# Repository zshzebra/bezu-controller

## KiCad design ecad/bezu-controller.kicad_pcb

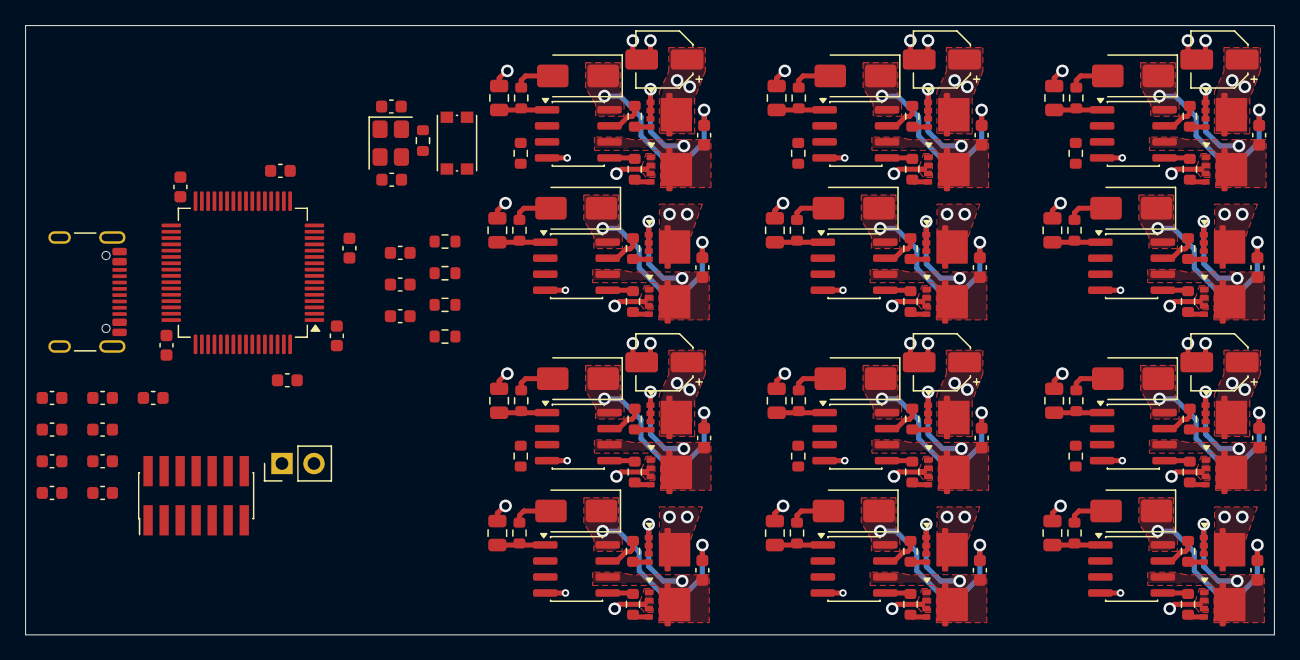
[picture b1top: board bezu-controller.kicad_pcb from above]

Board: 4 copper layers, 99.0 x 48.3 mm, 151 parts (0 on the bottom side), 109 nets.

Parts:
C1, C4, C7, C10, C13, C16, C19, C22, C25, C28, C31, C34: 470nF; C_0805_2012Metric
C2, C5, C8, C11, C14, C17, C20, C23, C26, C29, C32, C35: 47nF; C_0603_1608Metric
C6, C12, C18, C24, C30, C36: 4.7uF; CP_Elec_4x5.4
C37: 4.7uF; C_0603_1608Metric
C38, C39: 2.2uF; C_0603_1608Metric
C40, C41, C42, C43, C44, C45, C46, C47, C48, C49, C50, C51, C52, C53, C54: 100nF; C_0603_1608Metric
C55, C56: 16pF; C_0603_1608Metric
D1, D2, D3, D4, D5, D6, D7, D8, D9, D10, D11, D12: ES1D; D_SMA
J1: ST_STDC14; PinHeader_2x07_P1.27mm_Vertical_SMD
J2: GCT 4105; USB_C_Receptacle_GCT_USB4105-xx-A_16P_TopMnt_Horizontal
J3: Conn_01x02; PinHeader_1x02_P2.54mm_Vertical
Q1, Q2, Q3, Q4, Q5, Q6, Q7, Q8, Q9, Q10, Q11, Q12, Q13, Q14, Q15, Q16, Q17, Q18, Q19, Q20, Q21, Q22, Q23, Q24: 40N06D; PDFN3x3
R1, R8, R15, R22, R29, R36, R43, R47: 10K; R_0603_1608Metric
R2, R5, R9, R12, R16, R19, R23, R26, R30, R33, R37, R40: 2.2R; R_0603_1608Metric
R3, R4, R6, R7, R10, R11, R13, R14, R17, R18, R20, R21, R24, R25, R27, R28, R31, R32, R34, R35, R38, R39, R41, R42: 10R; R_0603_1608Metric
R44: 100R; R_0603_1608Metric
R45, R46: 5k1; R_0603_1608Metric
SW1: SW_Push; SW_Push_1P1T_NO_CK_KMR2
U1, U2, U3, U4, U5, U6, U7, U8, U9, U10, U11, U12: IR2104; SOIC-8_3.9x4.9mm_P1.27mm
U13: STM32F405RGTx; LQFP-64_10x10mm_P0.5mm
Y1: 12MHz; Crystal_SMD_3225-4Pin_3.2x2.5mm

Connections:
+3.3V: C37.1, C40.1, C41.1, C42.1, C43.1, C44.1, C45.1, C46.1, C47.1, C48.1, C49.1, C50.1, C51.1, C52.1, C53.1, C54.1, J1.3 (VCC), R43.1, R47.1, U13.1 (VBAT), U13.13 (VDDA), U13.19 (VDD), U13.32 (VDD), U13.48 (VDD), U13.64 (VDD)
+5V: J2.A4 (VBUS), J2.A9 (VBUS), J2.B4 (VBUS), J2.B9 (VBUS)
+12V: C1.1, C4.1, C7.1, C10.1, C13.1, C16.1, C19.1, C22.1, C25.1, C28.1, C31.1, C34.1, R2.1, R5.1, R9.1, R12.1, R16.1, R19.1, R23.1, R26.1, R30.1, R33.1, R37.1, R40.1, U1.1 (VCC), U2.1 (VCC), U3.1 (VCC), U4.1 (VCC), U5.1 (VCC), U6.1 (VCC), U7.1 (VCC), U8.1 (VCC), U9.1 (VCC), U10.1 (VCC), U11.1 (VCC), U12.1 (VCC)
/-PITCH H-Bridge/OUT1: C2.2, Q1.S, Q2.D, U1.6 (VS)
/-PITCH H-Bridge/OUT2: C5.2, Q3.S, Q4.D, U2.6 (VS)
/-PITCH H-Bridge/~SD: R1.1, U1.3 (~SD), U2.3 (~SD)
/-ROLL H-Bridge1/OUT1: C14.2, Q9.S, Q10.D, U5.6 (VS)
/-ROLL H-Bridge1/OUT2: C17.2, Q11.S, Q12.D, U6.6 (VS)
/-ROLL H-Bridge1/~SD: R15.1, U5.3 (~SD), U6.3 (~SD)
/-YAW H-Bridge2/OUT1: C26.2, Q17.S, Q18.D, U9.6 (VS)
/-YAW H-Bridge2/OUT2: C29.2, Q19.S, Q20.D, U10.6 (VS)
/-YAW H-Bridge2/~SD: R29.1, U9.3 (~SD), U10.3 (~SD)
/MCU/BOOT0: J3.1, R47.2, U13.60 (BOOT0)
/MCU/PH0: C56.1, U13.5 (PH0), Y1.3
/MCU/PH1: C55.1, U13.6 (PH1), Y1.1
/MCU/SWCLK: J1.6 (JCLK/SWCLK), U13.49 (PA14)
/MCU/SWDIO: J1.4 (JTMS/SWDIO), U13.46 (PA13)
/MCU/SWO: J1.8 (JTDO/SWO), U13.55 (PB3)
/MCU/USB_DM: J2.A7 (D-), J2.B7 (D-), U13.44 (PA11)
/MCU/USB_DP: J2.A6 (D+), J2.B6 (D+), U13.45 (PA12)
/PITCH H-Bridge1/OUT1: C8.2, Q5.S, Q6.D, U3.6 (VS)
/PITCH H-Bridge1/OUT2: C11.2, Q7.S, Q8.D, U4.6 (VS)
/PITCH H-Bridge1/~SD: R8.1, U3.3 (~SD), U4.3 (~SD)
/ROLL H-Bridge2/OUT1: C20.2, Q13.S, Q14.D, U7.6 (VS)
/ROLL H-Bridge2/OUT2: C23.2, Q15.S, Q16.D, U8.6 (VS)
/ROLL H-Bridge2/~SD: R22.1, U7.3 (~SD), U8.3 (~SD)
/YAW H-Bridge3/OUT1: C32.2, Q21.S, Q22.D, U11.6 (VS)
/YAW H-Bridge3/OUT2: C35.2, Q23.S, Q24.D, U12.6 (VS)
/YAW H-Bridge3/~SD: R36.1, U11.3 (~SD), U12.3 (~SD)
GND: C1.2, C4.2, C6.2, C7.2, C10.2, C12.2, C13.2, C16.2, C18.2, C19.2, C22.2, C24.2, C25.2, C28.2, C30.2, C31.2, C34.2, C36.2, C37.2, C38.2, C39.2, C40.2, C41.2, C42.2, C43.2, C44.2, C45.2, C46.2, C47.2, C48.2, C49.2, C50.2, C51.2, C52.2, C53.2, C54.2, C55.2, C56.2, J1.5 (GND), J1.7 (GND), J1.12 (~RST), J2.A1 (GND), J2.A12 (GND), J2.B1 (GND), J2.B12 (GND), J2.S1 (SHIELD), J3.2, Q2.S, Q4.S, Q6.S, Q8.S, Q10.S, Q12.S, Q14.S, Q16.S, Q18.S, Q20.S, Q22.S, Q24.S, R1.2, R8.2, R15.2, R22.2, R29.2, R36.2, R44.2, R45.2, R46.2, SW1.1, U1.4 (COM), U2.4 (COM), U3.4 (COM), U4.4 (COM), U5.4 (COM), U6.4 (COM), U7.4 (COM), U8.4 (COM), U9.4 (COM), U10.4 (COM), U11.4 (COM), U12.4 (COM), U13.12 (VSSA), U13.18 (VSS), U13.63 (VSS), Y1.2, Y1.4
unnamed: D1.2 (A), R2.2
unnamed: C2.1, D1.1 (K), U1.8 (VB)
unnamed: D2.2 (A), R5.2
unnamed: C5.1, D2.1 (K), U2.8 (VB)
unnamed: D3.2 (A), R9.2
unnamed: C8.1, D3.1 (K), U3.8 (VB)
unnamed: D4.2 (A), R12.2
unnamed: C11.1, D4.1 (K), U4.8 (VB)
unnamed: D5.2 (A), R16.2
unnamed: C14.1, D5.1 (K), U5.8 (VB)
unnamed: D6.2 (A), R19.2
unnamed: C17.1, D6.1 (K), U6.8 (VB)
unnamed: D7.2 (A), R23.2
unnamed: C20.1, D7.1 (K), U7.8 (VB)
unnamed: D8.2 (A), R26.2
unnamed: C23.1, D8.1 (K), U8.8 (VB)
unnamed: D9.2 (A), R30.2
unnamed: C26.1, D9.1 (K), U9.8 (VB)
unnamed: D10.2 (A), R33.2
unnamed: C29.1, D10.1 (K), U10.8 (VB)
unnamed: D11.2 (A), R37.2
unnamed: C32.1, D11.1 (K), U11.8 (VB)
unnamed: D12.2 (A), R40.2
unnamed: C35.1, D12.1 (K), U12.8 (VB)
unnamed: J1.11 (GNDDetect), R44.1
unnamed: J2.A5 (CC1), R45.1
unnamed: J2.B5 (CC2), R46.1
unnamed: Q1.G, R3.2
unnamed: Q2.G, R4.2
unnamed: Q3.G, R6.2
unnamed: Q4.G, R7.2
unnamed: Q5.G, R10.2
unnamed: Q6.G, R11.2
unnamed: Q7.G, R13.2
unnamed: Q8.G, R14.2
unnamed: Q9.G, R17.2
unnamed: Q10.G, R18.2
unnamed: Q11.G, R20.2
unnamed: Q12.G, R21.2
unnamed: Q13.G, R24.2
unnamed: Q14.G, R25.2
unnamed: Q15.G, R27.2
unnamed: Q16.G, R28.2
unnamed: Q17.G, R31.2
unnamed: Q18.G, R32.2
unnamed: Q19.G, R34.2
unnamed: Q20.G, R35.2
unnamed: Q21.G, R38.2
unnamed: Q22.G, R39.2
unnamed: Q23.G, R41.2
unnamed: Q24.G, R42.2
unnamed: R3.1, U1.7 (HO)
unnamed: R4.1, U1.5 (LO)
unnamed: R6.1, U2.7 (HO)
unnamed: R7.1, U2.5 (LO)
unnamed: R10.1, U3.7 (HO)
unnamed: R11.1, U3.5 (LO)
unnamed: R13.1, U4.7 (HO)
unnamed: R14.1, U4.5 (LO)
unnamed: R17.1, U5.7 (HO)
unnamed: R18.1, U5.5 (LO)
unnamed: R20.1, U6.7 (HO)
unnamed: R21.1, U6.5 (LO)
unnamed: R24.1, U7.7 (HO)
unnamed: R25.1, U7.5 (LO)
unnamed: R27.1, U8.7 (HO)
unnamed: R28.1, U8.5 (LO)
unnamed: R31.1, U9.7 (HO)
unnamed: R32.1, U9.5 (LO)
unnamed: R34.1, U10.7 (HO)
unnamed: R35.1, U10.5 (LO)
unnamed: R38.1, U11.7 (HO)
unnamed: R39.1, U11.5 (LO)
unnamed: R41.1, U12.7 (HO)
unnamed: R42.1, U12.5 (LO)
unnamed: R43.2, SW1.2, U13.7 (NRST)
unnamed: C39.1, U13.31 (VCAP_1)
unnamed: C38.1, U13.47 (VCAP_2)
Vdrive: C6.1, C12.1, C18.1, C24.1, C30.1, C36.1, Q1.D, Q3.D, Q5.D, Q7.D, Q9.D, Q11.D, Q13.D, Q15.D, Q17.D, Q19.D, Q21.D, Q23.D

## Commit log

2025-10-15 Use IRS2104
2025-10-15 Create PDFN-8-3x3 3d model
2025-10-15 Fix minor issue in PDFN-8-3x3 model
2025-10-17 Work on MOSFET driver
2025-11-16 Initial half bridge layout
2025-11-23 More work on layout
2025-11-23 Remove numbers frmo sheet instances
